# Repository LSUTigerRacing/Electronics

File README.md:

<div align="center">
    
</div>
<hr />
<div align="center">
    
</div>
<br />
<div align="center">
    This repository contains all of the KiCad Schematics for the TigerRacing Formula SAE's Electronics Subsystem.
</div>
<br />

## Prerequisites
* [Git](https://git-scm.com/downloads)
* [KiCad](https://www.kicad.org/download/)
* A [GitHub](https://github.com) account

## Board Templates
When making a new PCB, if the board is to be manufactured by **JLCPCB**. import the corresponding board constraints from `Board Templates/JLC` 

## Getting Started
This section will walk you through downloading the repository to your computer for the first time. You only need to do this once.

### 1. Generate a GitHub Token
A token is essentially a password that lets Git on your computer talk to GitHub securely.

1. Log into [GitHub](https://github.com)
2. Click your profile picture → **Settings**
3. Scroll down and click **Developer settings** (bottom of the left sidebar)
4. Click **Personal access tokens** → **Tokens (classic)**
5. Click **Generate new token (classic)**
6. Give it a name (e.g. `git-access`), set an expiration, and check the **repo** scope
7. Click **Generate token** and **copy it** — you won't be able to see it again!

### 2. Clone the Repository
"Cloning" means downloading a full copy of the repository to your computer.

Open **Git Bash** and run the following commands one at a time:
```sh
git clone https://github.com/LSUTigerRacing/Electronics.git
cd Electronics
```

When prompted for a password, paste the token you copied in the previous step.

### 3. Open the Project in KiCad
In **Git Bash**, highlight and right-click `Electronics` to open the folder in File Explorer. From there, open the KiCad project file (`.kicad_pro`).

---

## Contributing
This section covers the full workflow for making changes and submitting them every time you work on something.

> [!IMPORTANT]
> **Never commit directly to `main`.** All changes must go through a pull request.

### Step 1 — Make sure you're up to date
Before starting any work, pull the latest changes from the repository so you're not working on an outdated copy.
```sh
cd Electronics
git pull origin main
```

### Step 2 — Create a branch
A "branch" is your own isolated workspace. Think of it like making a photocopy of the project — you make your edits on the copy, and only merge it back once everything looks good.

Replace `your-branch-name` with something descriptive (e.g. `fault-latch-rework`).
```sh
git checkout -b "your-branch-name"
```

### Step 3 — Make your edits
Open the KiCad project and make your changes. Save your work when done.

### Step 4 — Stage and commit your changes
"Staging" tells Git which files to include, and "committing" saves a snapshot of those changes with a description.
```sh
git add .
git commit -m "Brief description of what you changed"
```

### Step 5 — Push your branch to GitHub
"Pushing" uploads your local branch so others (and GitHub) can see it.
```sh
git push -u origin "your-branch-name"
```

### Step 6 — Open a Pull Request
1. Go to the [repository on GitHub](https://github.com/LSUTigerRacing/Electronics)
2. Click the **Pull requests** tab
3. Click **New pull request**
4. Set the **base** branch to `main` and the **compare** branch to yours
5. Give it a clear title and description of what you changed
6. Click **Create pull request**

A reviewer will look over your changes. Once approved, your branch will be merged into `main` and can then be deleted.

---

## PCB Gallery

### Fault Latch

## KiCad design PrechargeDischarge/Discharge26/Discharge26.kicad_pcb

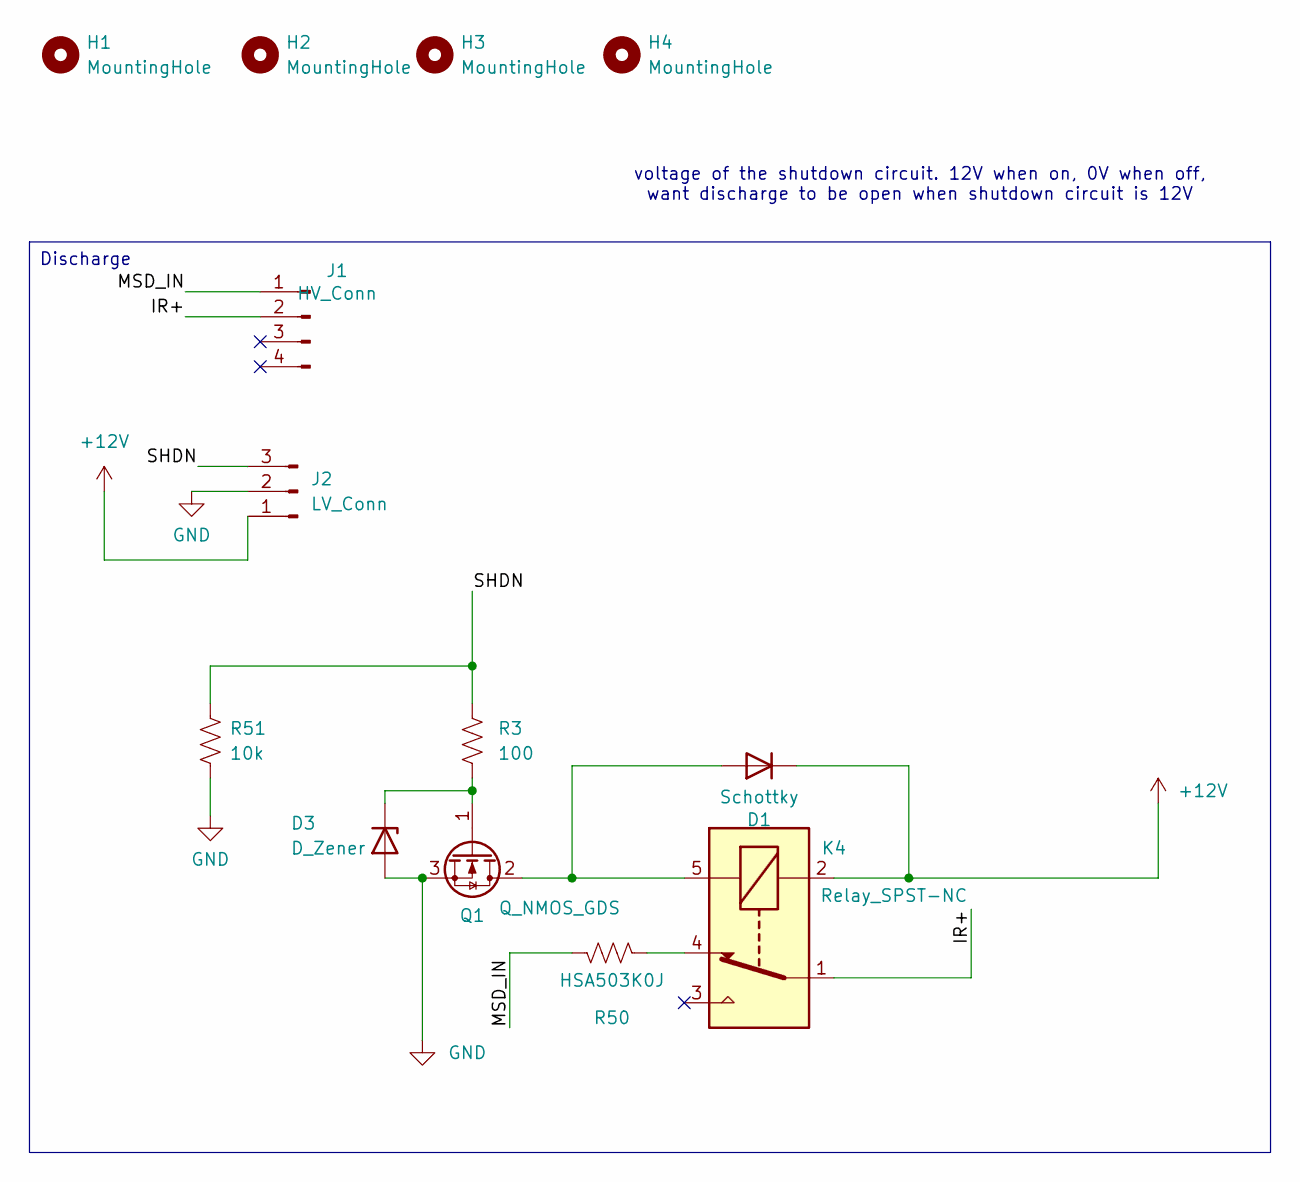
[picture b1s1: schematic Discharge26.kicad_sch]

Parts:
D1: Schottky; D_SMA; JLC C8678
D3: D_Zener; D_SOD-123; JLC C241967
H1, H2, H3, H4: MountingHole; MountingHole_4.3mm_M4
J1: HV_Conn; MicroFit_4pin
J2: LV_Conn; Molex_Nano-Fit_105313-xx03_1x03_P2.50mm_Horizontal; JLC C561764
K4: Relay_SPST-NC; Discharge_relay
Q1: Q_NMOS_GDS; TO-251-3_Vertical; JLC C3278986
R3: 100; R_0805_2012Metric_Pad1.20x1.40mm_HandSolder; JLC C17408
R50: HSA503K0J; Discharge_Resistor
R51: 10k; R_1206_3216Metric

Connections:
+12V: D1.1 (K), J2.1, K4.2
/IR+: J1.2, K4.1
/MSD_IN: J1.1, R50.2
/SHDN: J2.3, R3.1, R51.1
GND: D3.2 (A), J2.2, Q1.3 (S), R51.2
unnamed: D1.2 (A), K4.5, Q1.2 (D)
unnamed: D3.1 (K), Q1.1 (G), R3.2
unnamed: K4.4, R50.1

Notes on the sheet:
voltage of the shutdown circuit. 12V when on, 0V when off, want discharge to be open when shutdown circuit is 12V
Discharge

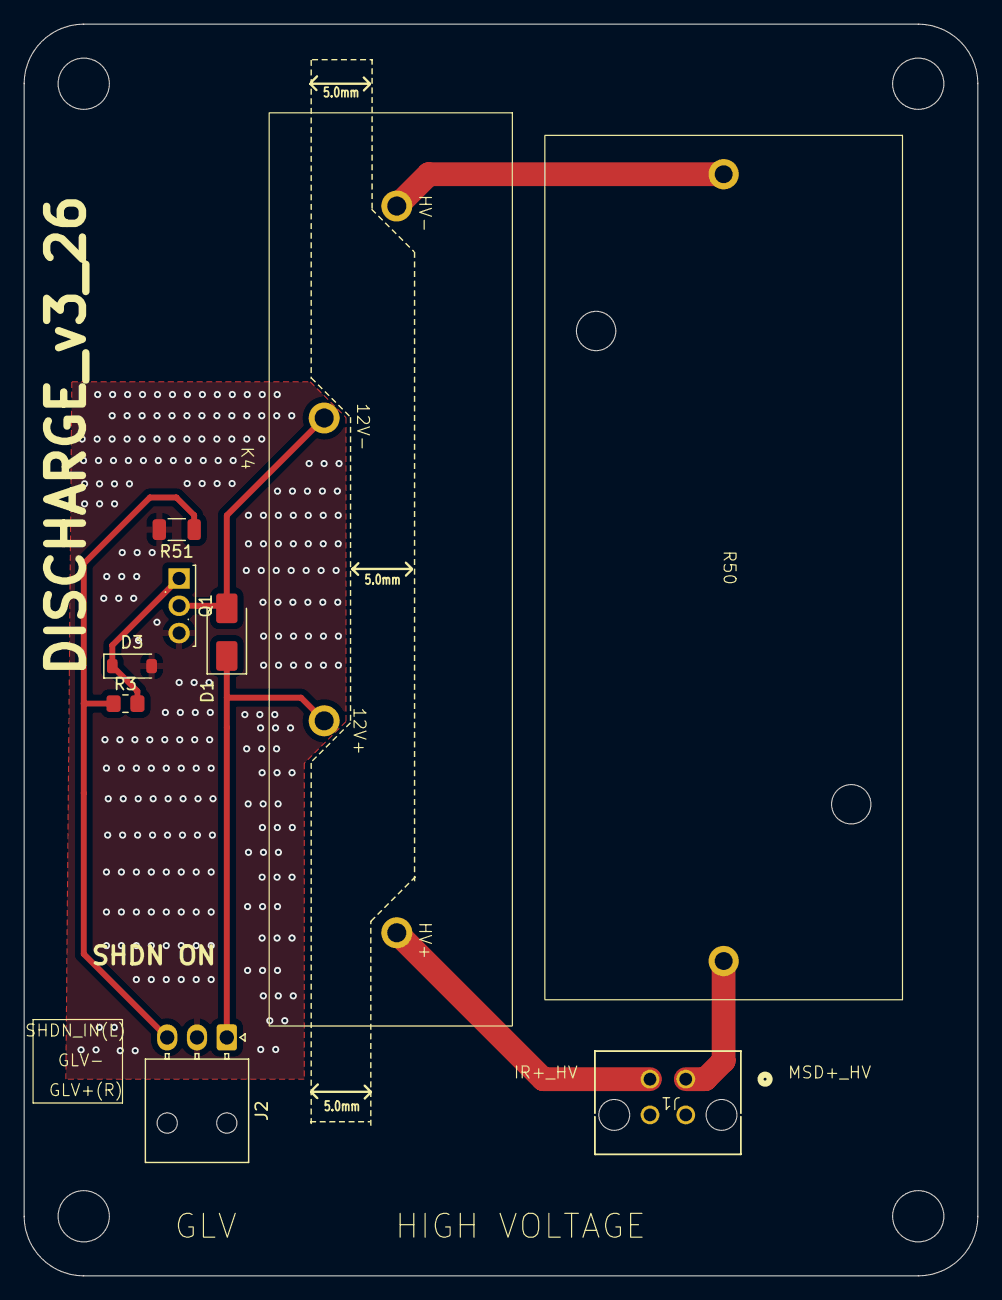
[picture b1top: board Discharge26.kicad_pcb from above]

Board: 2 copper layers, 80.0 x 105.0 mm, 13 parts (0 on the bottom side), 8 nets.

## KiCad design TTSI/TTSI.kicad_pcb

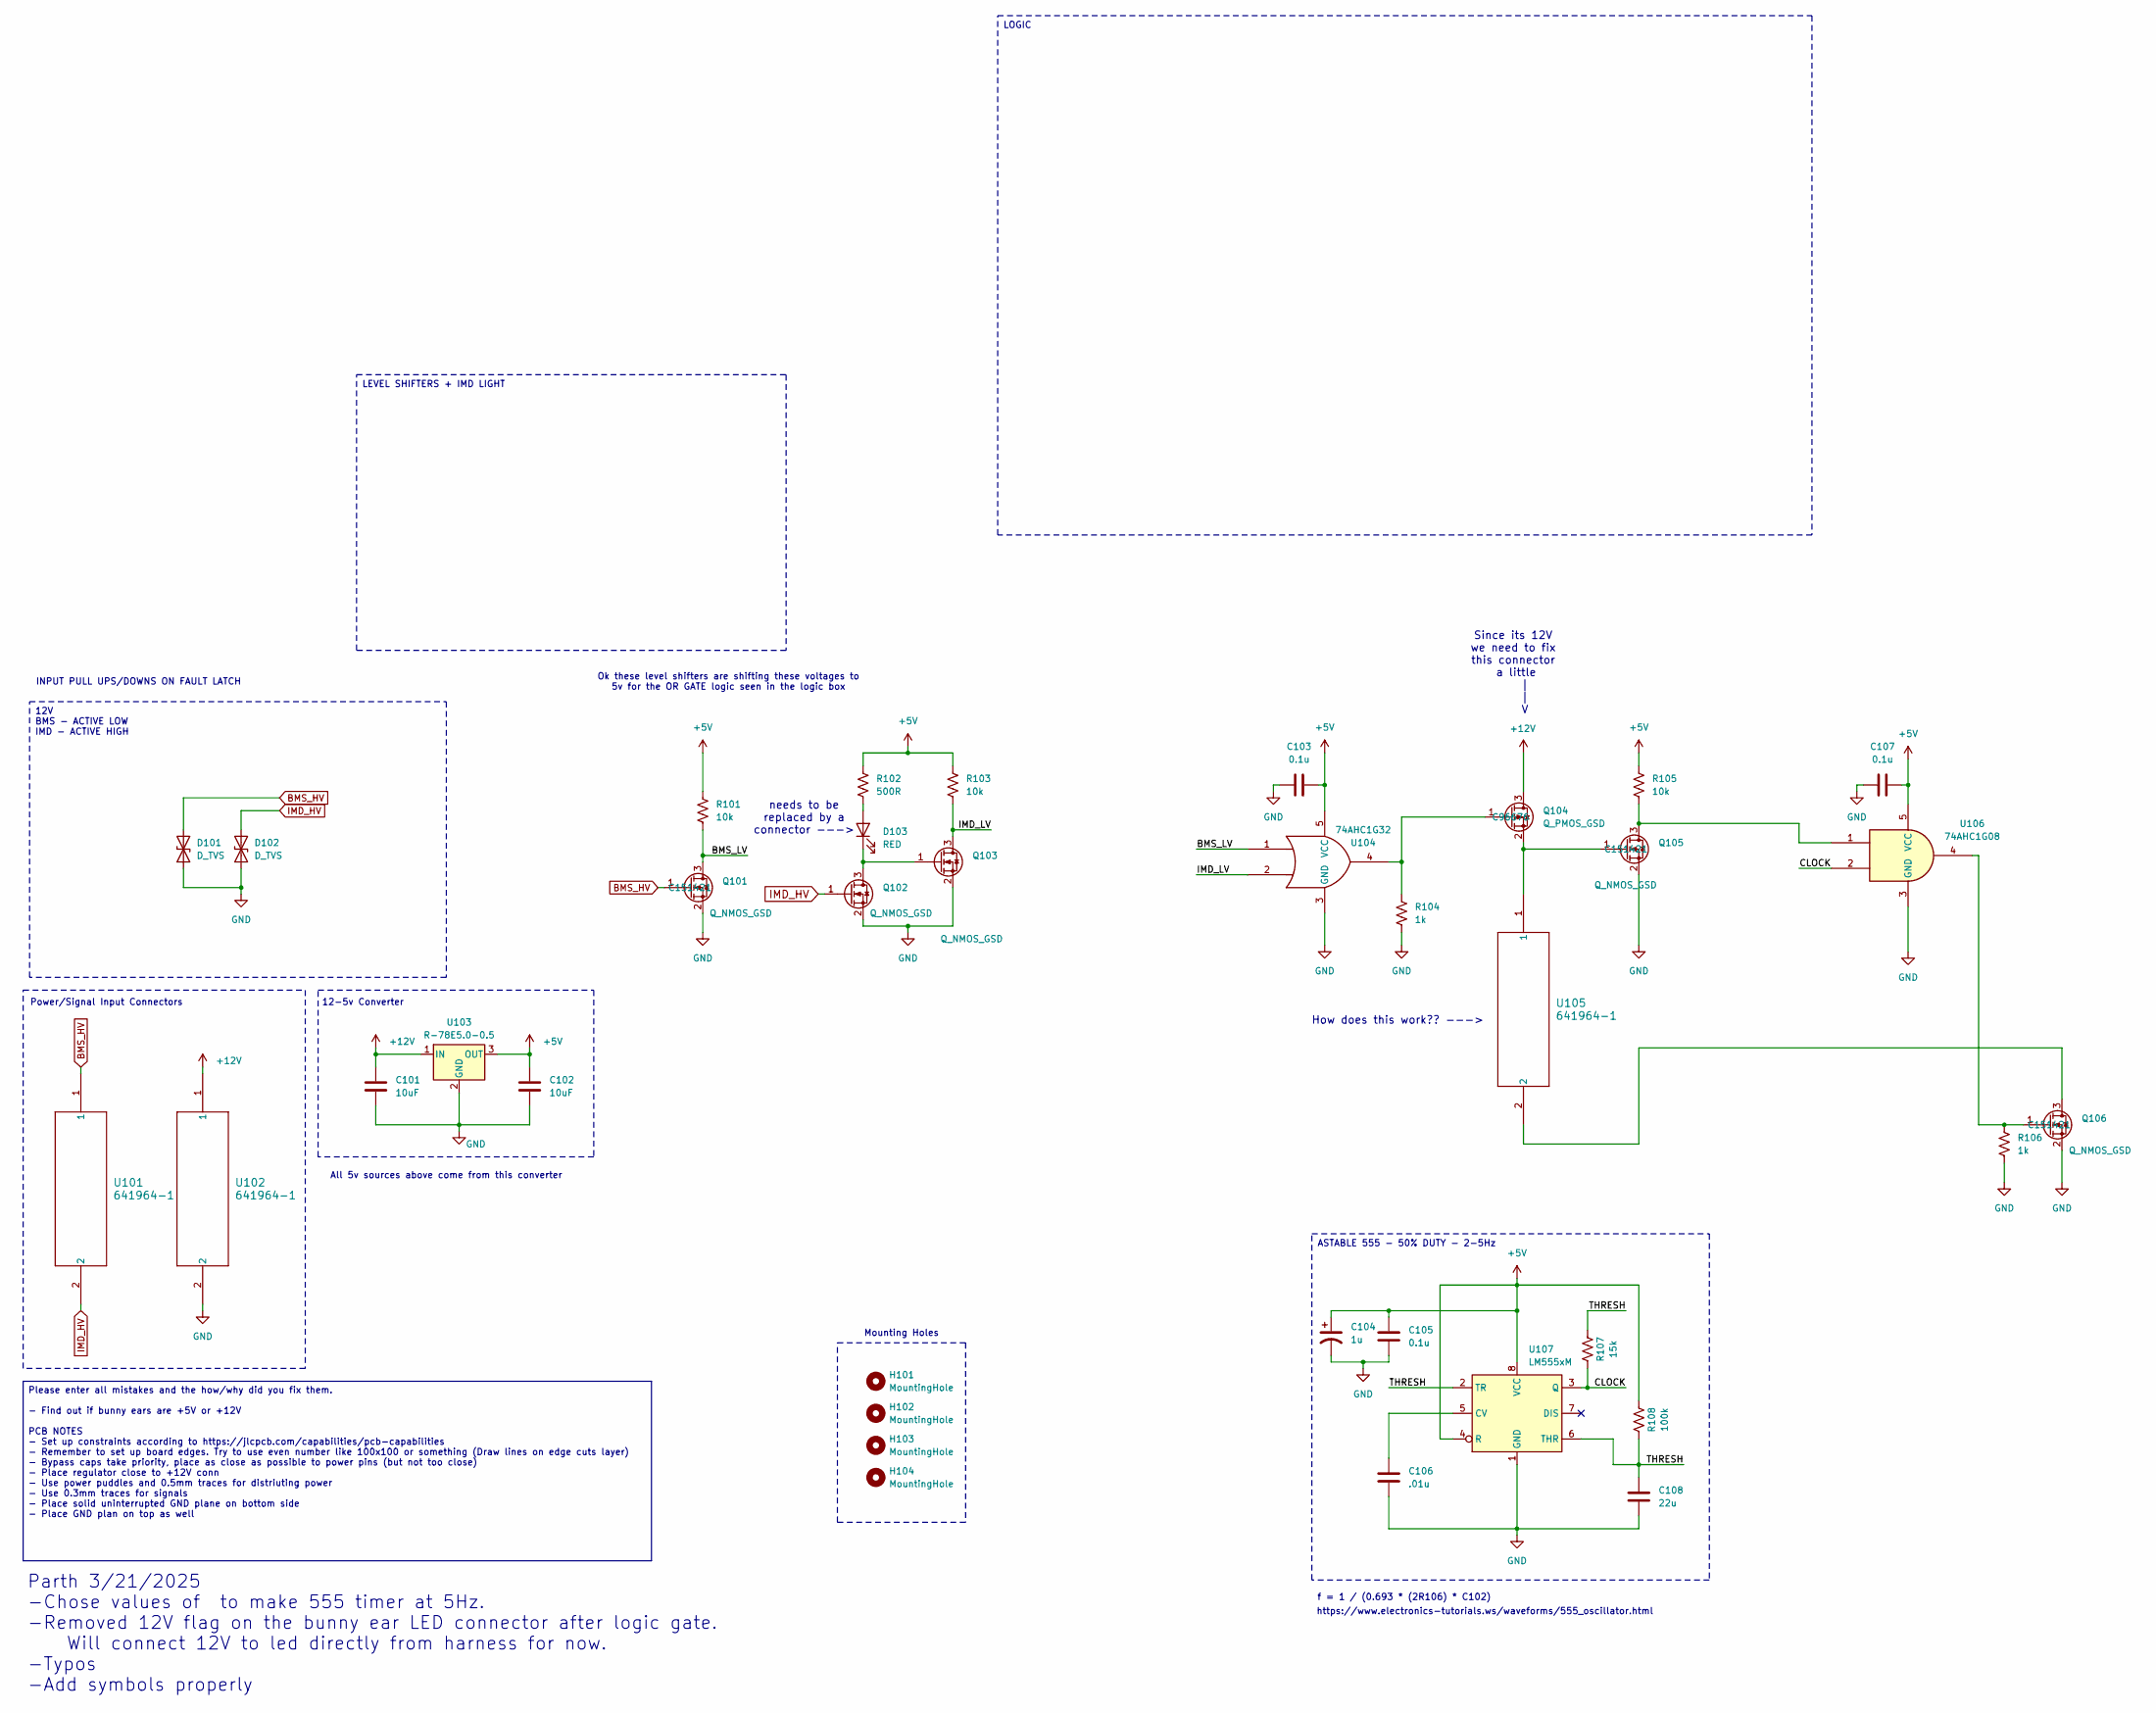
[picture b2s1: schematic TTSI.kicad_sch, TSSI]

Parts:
C101, C102: 10uF; C_0402_1005Metric; JLC# C307520
C103, C105, C107: 0.1u; C_0402_1005Metric; JLC# C133086
C104: 1u; C_0402_1005Metric; JLC# C59782
C106: .01u; C_0402_1005Metric; JLC# C15195
C108: 22u; C_0402_1005Metric
D101, D102: D_TVS; D_SOD-123F; JLC# C110748
D103: RED; R_0603_1608Metric; JLC# C3030991
H101, H102, H103, H104: MountingHole; MountingHole_2.2mm_M2
Q101, Q102, Q103, Q105, Q106: Q_NMOS_GSD; SOT-23; JLC# C151421
Q104: Q_PMOS_GSD; SOT-523; JLC# C96676
R101, R103, R105: 10k; R_0603_1608Metric; JLC# C130232
R102: 500R; R_0603_1608Metric; JLC# C130232
R104, R106: 1k; R_0603_1608Metric; JLC# C105637
R107: 15k; R_0603_1608Metric
R108: 100k; R_0603_1608Metric; JLC# C60491
U101, U102, U105: 641964-1; 641964-1_TYC
U103: R-78E5.0-0.5; R-78E-0.5_RCP; JLC# C5199916
U104: 74AHC1G32; SOT-353_SC-70-5; JLC# C7394028
U106: 74AHC1G08; SOT-353_SC-70-5; JLC# C2861162
U107: LM555xM; SOIC-8_3.9x4.9mm_P1.27mm; JLC# C90760

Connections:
+5V: C102.1, C103.1, C104.1, C105.1, C107.1, R101.1, R102.1, R103.1, R105.1, R108.2, U103.3 (OUT), U104.5 (VCC), U106.5 (VCC), U107.4 (R), U107.8 (VCC)
+12V: C101.1, Q104.3 (D), U102.1, U103.1 (IN)
/BMS_LV: Q101.3 (D), R101.2, U104.1
/CLOCK: R107.1, U106.2, U107.3 (Q)
/IMD_LV: Q103.3 (D), R103.2, U104.2
/THRESH: C108.2, R107.2, R108.1, U107.2 (TR), U107.6 (THR)
BMS_HV: D101.2 (A2), Q101.1 (G), U101.1
GND: C101.2, C102.2, C103.2, C104.2, C105.2, C106.2, C107.2, C108.1, D101.1 (A1), D102.1 (A1), Q101.2 (S), Q102.2 (S), Q103.2 (S), Q105.2 (S), Q106.2 (S), R104.2, R106.2, U102.2, U103.2 (GND), U104.3 (GND), U106.3 (GND), U107.1 (GND)
IMD_HV: D102.2 (A2), Q102.1 (G), U101.2
unnamed: D103.2 (A), R102.2
unnamed: D103.1 (K), Q102.3 (D), Q103.1 (G)
unnamed: Q104.1 (G), R104.1, U104.4
unnamed: Q104.2 (S), Q105.1 (G), U105.1
unnamed: Q105.3 (D), R105.2, U106.1
unnamed: Q106.3 (D), U105.2
unnamed: Q106.1 (G), R106.1, U106.4
unnamed: C106.1, U107.5 (CV)

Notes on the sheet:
Mounting Holes
All 5v sources above come from this converter
f = 1 / (0.693 * (2R106) * C102)
INPUT PULL UPS/DOWNS ON FAULT LATCH
needs to be replaced by a connector --->
Since its 12V we need to fix this connector a little | | V
Power/Signal Input Connectors
Parth 3/21/2025 -Chose values of to make 555 timer at 5Hz. -Removed 12V flag on the bunny ear LED connector after logic gate. Will connect 12V to led directly from harness for now. -Typos -Add symbols properly
Ok these level shifters are shifting these voltages to 5v for the OR GATE logic seen in the logic box
12-5v Converter
https://www.electronics-tutorials.ws/waveforms/555_oscillator.html
How does this work?? --->
LEVEL SHIFTERS + IMD LIGHT
ASTABLE 555 - 50% DUTY - 2-5Hz
LOGIC
12V BMS - ACTIVE LOW IMD - ACTIVE HIGH
Please enter all mistakes and the how/why did you fix them. - Find out if bunny ears are +5V or +12V PCB NOTES - Set up constraints according to https://jlcpcb.com/capabilities/pcb-capabilities - Remember to set up board edges. Try to use even number like 100x100 or something (Draw lines on edge cu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

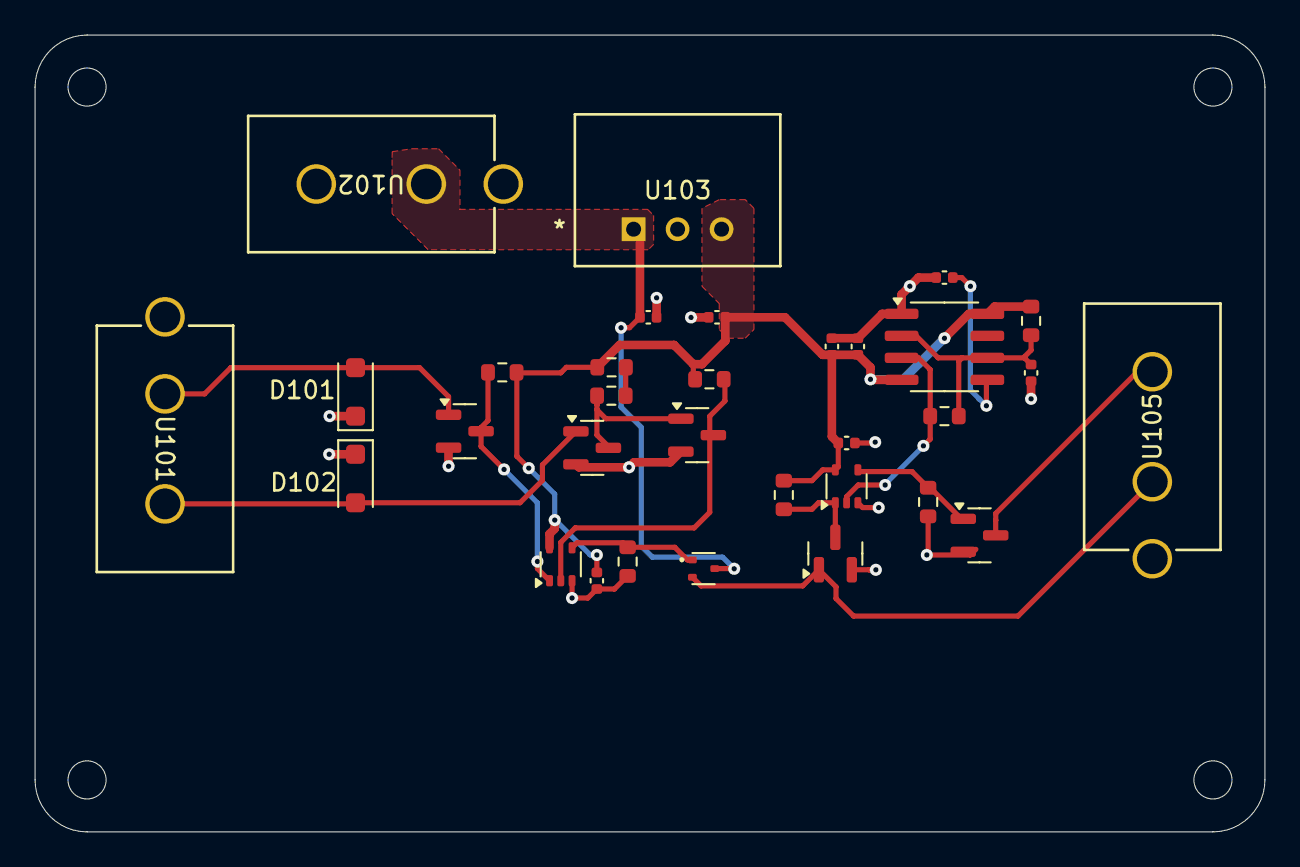
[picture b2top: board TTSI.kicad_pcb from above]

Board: 2 copper layers, 71.0 x 46.0 mm, 36 parts (0 on the bottom side), 17 nets.

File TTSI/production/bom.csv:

Designator,Footprint,Quantity,Value,LCSC Part #
"C101, C102",0402,2,10uF,
"C103, C105, C107",0402,3,0.1u,
C104,0402,1,1u,
C106,0402,1,.01u,
C108,0402,1,22u,
"D101, D102",D_SOD-123F,2,D_TVS,
D103,0603,1,RED,
"Q101, Q102, Q103, Q105, Q106",SOT-23,5,Q_NMOS_GSD,
Q104,SOT-523,1,Q_PMOS_GSD,
"R101, R103, R105",0603,3,10k,
R102,0603,1,500R,
"R104, R106",0603,2,1k,
R107,0603,1,15k,
R108,0603,1,100k,
"U101, U102, U105",641964-1_TYC,3,641964-1,
U103,R-78E-0.5_RCP,1,R-78E5.0-0.5,
U104,SOT-353_SC-70-5,1,74AHC1G32,
U106,SOT-353_SC-70-5,1,74AHC1G08,
U107,SOIC-8_3.9x4.9mm_P1.27mm,1,LM555xM,

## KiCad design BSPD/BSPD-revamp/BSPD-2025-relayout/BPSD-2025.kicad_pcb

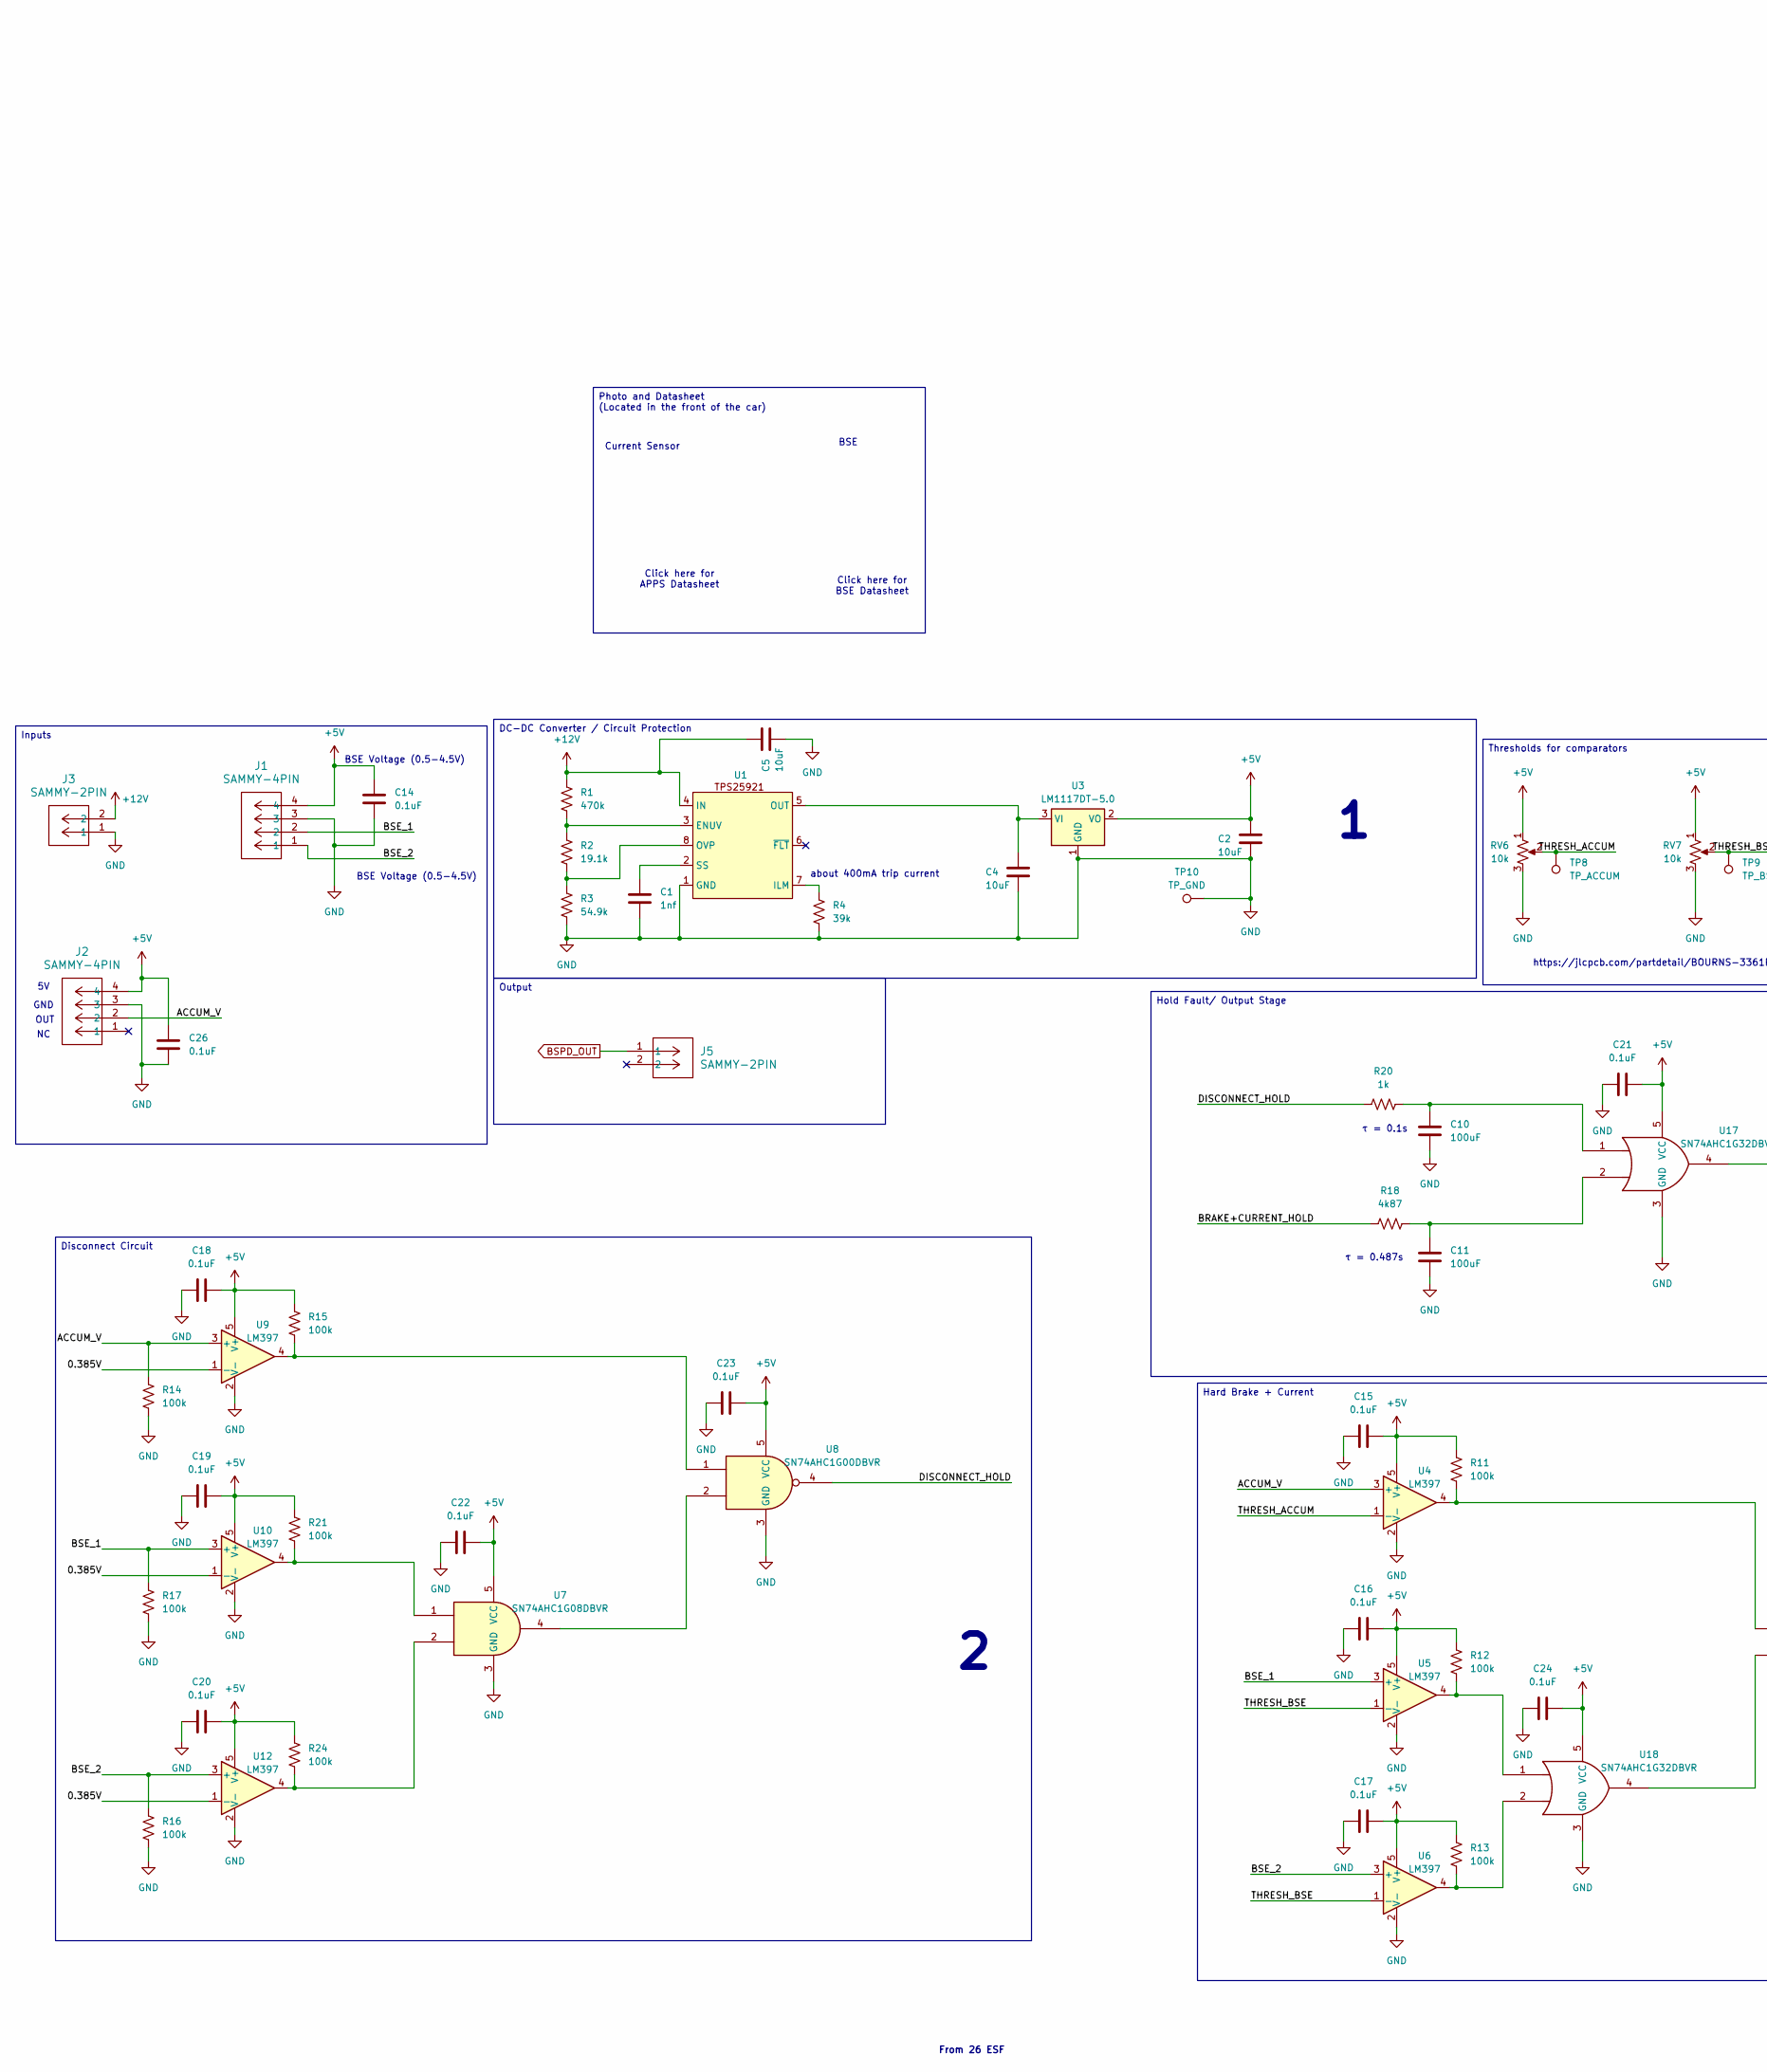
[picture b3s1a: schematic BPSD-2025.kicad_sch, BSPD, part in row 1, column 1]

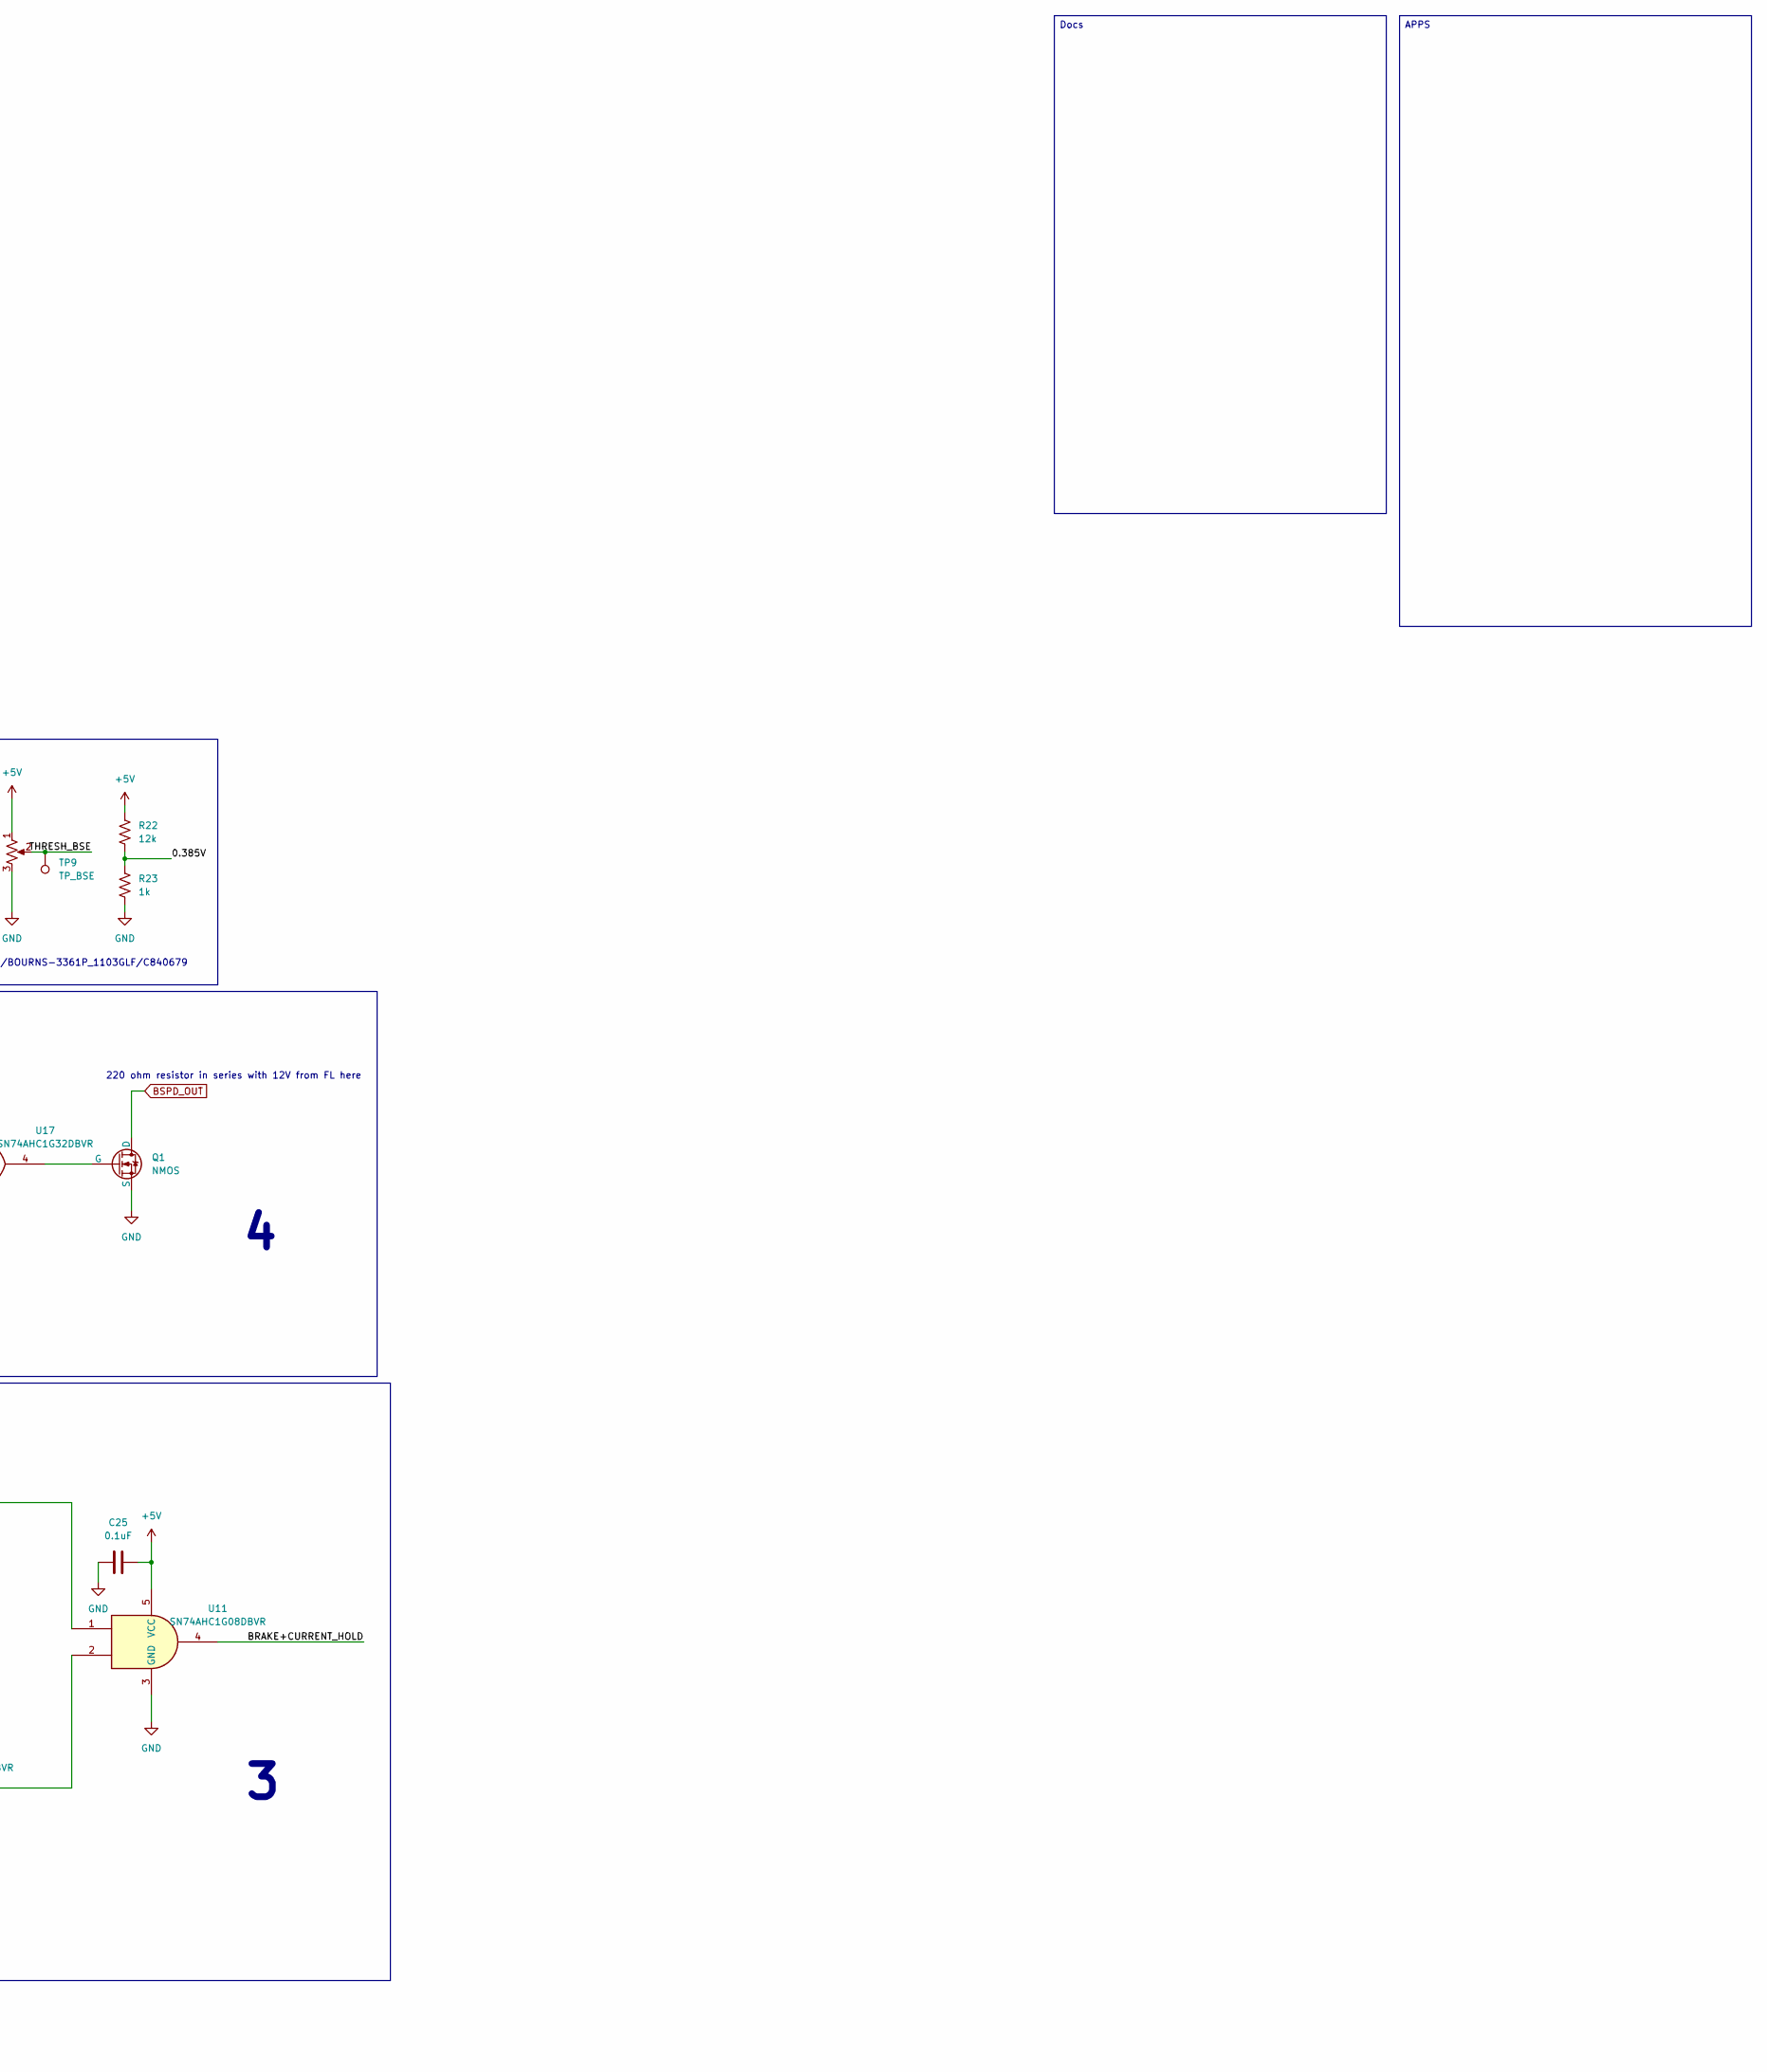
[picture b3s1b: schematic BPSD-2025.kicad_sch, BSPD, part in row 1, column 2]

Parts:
C1: 1nf; C_1206_3216Metric; JLC# C1845
C2, C4, C5: 10uF; C_1206_3216Metric; JLC# C1849
C10, C11: 100uF; C_1206_3216Metric; JLC# C782156
C14, C15, C16, C17, C18, C19, C20, C21, C22, C23, C24, C25, C26: 0.1uF; C_1206_3216Metric; JLC# C24497
J1, J2: SAMMY-4PIN
J3, J5: SAMMY-2PIN
Q1: NMOS; SOT-23; JLC# C151421
R1: 470k; R_1210_3225Metric; JLC# C48392111
R2: 19.1k; R_1210_3225Metric; JLC# C784281
R3: 54.9k; R_1206_3216Metric; JLC# C323092
R4: 39k; R_1210_3225Metric; JLC# C728378
R11, R12, R13, R14, R15, R16, R17, R21, R24: 100k; R_1210_3225Metric; JLC# C185765
R18: 4k87; R_1210_3225Metric; JLC# C3000590
R20, R23: 1k; R_1210_3225Metric
R22: 12k; R_1210_3225Metric; JLC# C182355
RV6, RV7: 10k; Potentiometer_Bourns_3296W_Vertical; JLC# C118954
TP8: TP_ACCUM; TestPoint_Pad_D1.5mm
TP9: TP_BSE; TestPoint_Pad_D1.5mm
TP10: TP_GND; TestPoint_Pad_D1.5mm
U1: SOIC-8_3.9x4.9mm_P1.27mm; JLC# C189199
U3: LM1117DT-5.0; TO-252-3_TabPin2
U4, U5, U6, U9, U10, U12: LM397; SOT-23-5; JLC# C132076
U7, U11: SN74AHC1G08DBVR; SOT-23-5; JLC# C7467
U8: SN74AHC1G00DBVR; SOT-23-5; JLC# C350556
U17, U18: SN74AHC1G32DBVR; SOT-23-5; JLC# C7470

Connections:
+5V: C2.1, C14.1, C15.2, C16.2, C17.2, C18.2, C19.2, C20.2, C21.2, C22.2, C23.2, C24.2, C25.2, C26.1, J1.4, J2.4, R11.2, R12.2, R13.2, R15.2, R21.2, R22.2, R24.2, RV6.1, RV7.1, U3.2 (VO), U4.5 (V+), U5.5 (V+), U6.5 (V+), U7.5 (VCC), U8.5 (VCC), U9.5 (V+), U10.5 (V+), U11.5 (VCC), U12.5 (V+), U17.5 (VCC), U18.5 (VCC); also elsewhere on the board
+12V: C5.1, J3.2, R1.1, U1.4 (IN)
/0.385V: R22.1, R23.2, U9.1 (-), U10.1 (-), U12.1 (-)
/ACCUM_V: J2.2, R14.2, U4.3 (+), U9.3 (+); also elsewhere on the board
/BRAKE+CURRENT_HOLD: R18.1, U11.4
/BSE_1: J1.2, R17.2, U5.3 (+), U10.3 (+); also elsewhere on the board
/BSE_2: J1.1, R16.2, U6.3 (+), U12.3 (+); also elsewhere on the board
/DISCONNECT_HOLD: R20.1, U8.4
/THRESH_ACCUM: RV6.2, TP8.1, U4.1 (-)
/THRESH_BSE: RV7.2, TP9.1, U5.1 (-), U6.1 (-)
BSPD_OUT: J5.1, Q1.1 (D)
GND: C1.2, C2.2, C4.2, C5.2, C10.2, C11.2, C14.2, C15.1, C16.1, C17.1, C18.1, C19.1, C20.1, C21.1, C22.1, C23.1, C24.1, C25.1, C26.2, J1.3, J2.3, J3.1, Q1.3 (S), R3.2, R4.2, R14.1, R16.1, R17.1, R23.1, RV6.3, RV7.3, TP10.1, U1.1 (GND), U3.1 (GND), U4.2 (V-), U5.2 (V-), U6.2 (V-), U7.3 (GND), U8.3 (GND), U9.2 (V-), U10.2 (V-), U11.3 (GND), U12.2 (V-), U17.3 (GND), U18.3 (GND); also elsewhere on the board
unnamed: C10.1, R20.2, U17.1
unnamed: C11.1, R18.2, U17.2
unnamed: Q1.2 (G), U17.4
unnamed: R11.1, U4.4, U11.1
unnamed: R12.1, U5.4, U18.1
unnamed: R13.1, U6.4, U18.2
unnamed: R15.1, U8.1, U9.4
unnamed: R21.1, U7.1, U10.4
unnamed: R24.1, U7.2, U12.4
unnamed: R1.2, R2.1, U1.3 (ENUV)
unnamed: R4.1, U1.7 (ILM)
unnamed: C4.1, U1.5 (OUT), U3.3 (VI)
unnamed: R2.2, R3.1, U1.8 (OVP)
unnamed: C1.1, U1.2 (SS)
unnamed: U7.4, U8.2
unnamed: U11.2, U18.4

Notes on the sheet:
BSE Voltage (0.5-4.5V)
BSE
GND
220 ohm resistor in series with 12V from FL here
about 400mA trip current
τ = 0.1s
Click here for APPS Datasheet
OUT
https://jlcpcb.com/partdetail/BOURNS-3361P_1103GLF/C840679
τ = 0.487s
From 26 ESF
Current Sensor
Click here for BSE Datasheet
Inputs
Hard Brake + Current
Docs
APPS
Photo and Datasheet (Located in the front of the car)
DC-DC Converter / Circuit Protection
Disconnect Circuit
Hold Fault/ Output Stage
Thresholds for comparators
Output

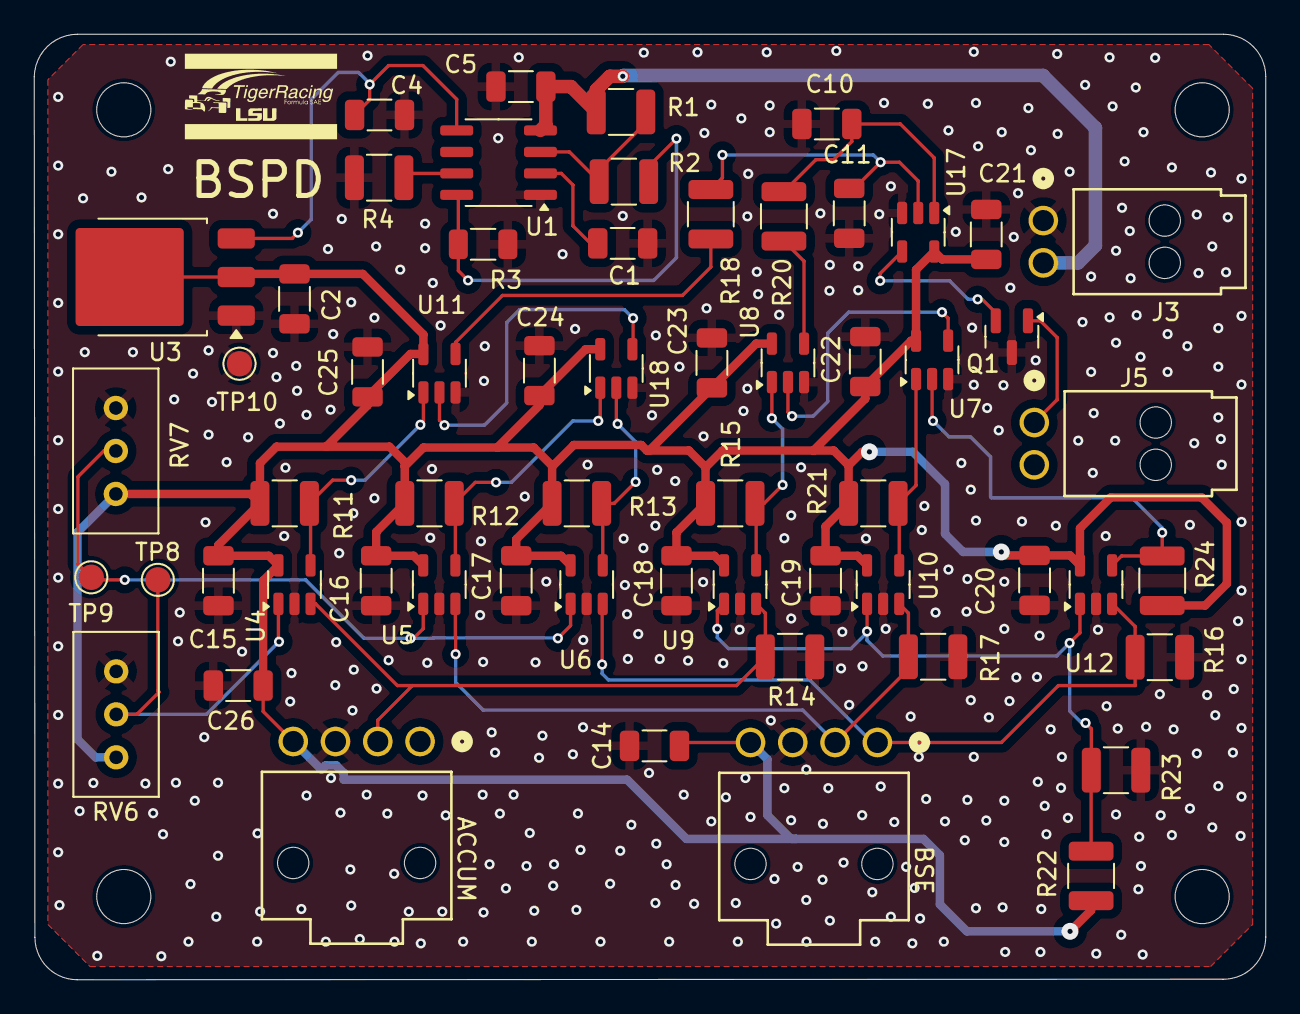
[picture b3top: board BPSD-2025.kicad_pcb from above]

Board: 2 copper layers, 72.8 x 55.9 mm, 59 parts (0 on the bottom side), 28 nets.

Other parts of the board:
ACCUM: SAMMY-4PIN
BSE: SAMMY-4PIN

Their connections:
+5V: ACCUM.4, BSE.4; also elsewhere on the board
/ACCUM_V: ACCUM.2; also elsewhere on the board
/BSE_1: BSE.2; also elsewhere on the board
/BSE_2: BSE.1; also elsewhere on the board
GND: ACCUM.3, BSE.3; also elsewhere on the board
